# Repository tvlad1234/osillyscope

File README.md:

# osillyscope
CH32V003 OLED screen oscilloscope

 **Many thanks to [PCBway](https://www.pcbway.com/) for sponsoring this project with fast high-quality PCB prototyping.**

This is a small digital oscilloscope based around the CH32V003A4M6 RISC-V microcontroller. It uses an SSD1306 I2C OLED display and three pushbuttons for the user interface. Its purpose is to be an inexpensive, easy to build and pocket-sized tool for checking the presence, levels and waveform of an unknown signal. The hardware design focuses on simplicity and low-count bill of materials.

The maximum achievable sample rate is 1.6MSa/s (the time base goes as low as 5us/div). This project proposes a frontend design which allows for a signal input range between -3.3V and +3.3V. The input range can be extended using a standard 10x probe, as the instrument has 1MOhm of input impedance. The bandwidth of the frontend was measured to be around 2.5MHz. 

## Hardware
The schematics and board design files (KiCad 7) are provided in the [hw](hw) folder. Two PCB designs are included: [a 2-layer design, meant to be sent to a PCB fab](hw/osillyscope-2layer/) and [a single layer one, designed to be easily etchable](hw/osillyscope-etchable/).

### **PCBs**

Very shortly after I had published this project, PCBWay reached out to me, offering to try their PCB prototyping services. About a week after placing the order, the boards had arrived, and here are my thoughts on the service they provided:

I'm very pleased with them. They feel dense and solid, I had absolutely no trouble soldering them up. With such a relatively simple, untested board design, I chose to go with HASL finish. While assembling, I had to desolder and resolder the power pin header, and the pads didn't show any signs of possible failure or fatigue (I had that happen often with various circuit boards in the past, but I had no issues with these ones). Visually, I opted for black solder mask. It looks absolutely beautiful, glossy and uniformly coated, honestly the picture above doesn't show it in all of its beauty. The silkscreen is crisp, precise and nicely aligned.

Ordering from them was quite a breeze using their KiCad plugin, which automatically plots and uploads the Gerber files into their ordering platform with a single click. I find their service affordable, I ordered 10 boards (2 layers, 1.6mm with HASL finish) and the price for the boards came to be 5USD.

This was my first experience with PCBWay's prototyping service, and it's been a pleasant one. I will certainly consider them again for my next PCB prototyping needs, and I warmly encourage you too will give them a try.

### Circuitry  
The analog frontend consists of a 2x attenuator, opamp buffer stage and DC offset stage. An ICL7660 voltage converter IC provides the negative supply voltage for the TL082 dual opamp. The oscilloscope can be powered from a 5 or more volts supply, such as a 9V battery.

The schematics are also provided as PDF, in [doc/schematic.pdf](doc/schematic.pdf).

## Code
The firmware source code is provided in the [fw](fw) folder. It uses the [ch32fun](https://github.com/cnlohr/ch32fun/) framework.

The ADC operates in continuous conversion mode and samples are fetched into a circular buffer via DMA. Triggering is achieved using the analog watchdog feature of the ADC.

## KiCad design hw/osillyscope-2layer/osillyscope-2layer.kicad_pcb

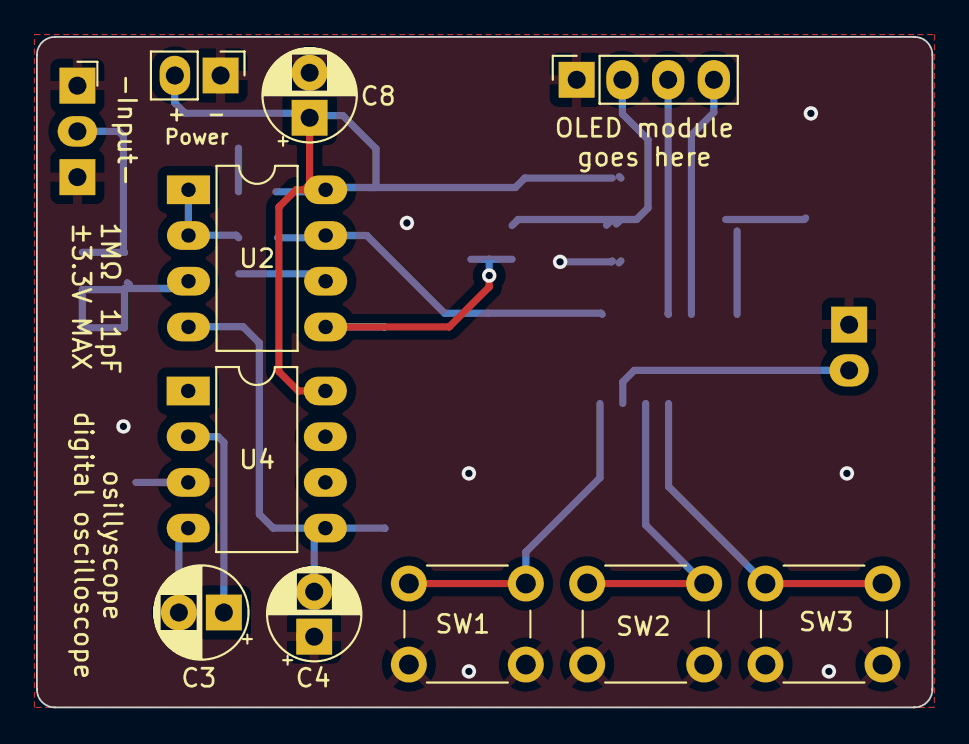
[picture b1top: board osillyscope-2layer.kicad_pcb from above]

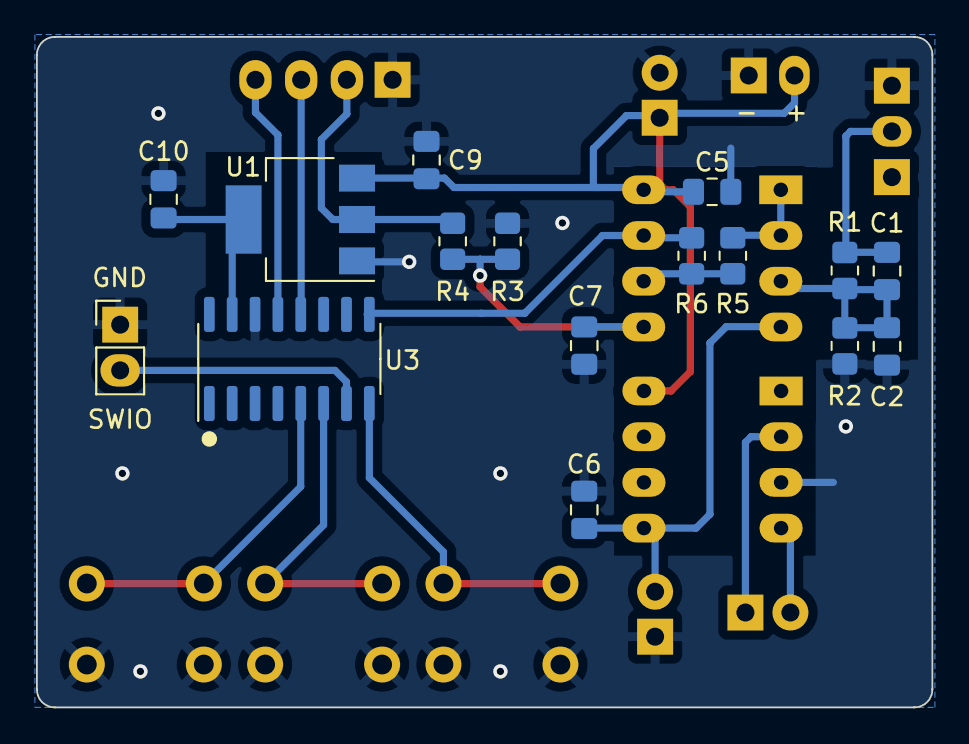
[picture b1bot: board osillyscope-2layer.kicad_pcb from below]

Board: 2 copper layers, 49.8 x 37.2 mm, 27 parts (16 on the bottom side), 18 nets.

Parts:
C1, C2: 22p; C_0805_2012Metric_Pad1.18x1.45mm_HandSolder
C3, C4: 10u; CP_Radial_D5.0mm_P2.50mm
C5, C6, C7, C9, C10: 100n; C_0805_2012Metric_Pad1.18x1.45mm_HandSolder
C8: 100u; CP_Radial_D5.0mm_P2.50mm
J1: IN; PinSocket_1x03_P2.54mm_Horizontal
J2: OLED; PinSocket_1x04_P2.54mm_Vertical
J3: Conn_01x02; PinHeader_1x02_P2.54mm_Vertical
J4: Debug/Prog; PinHeader_1x02_P2.54mm_Vertical
R1, R2: 500k; R_0805_2012Metric_Pad1.20x1.40mm_HandSolder
R3, R5, R6: 20k; R_0805_2012Metric_Pad1.20x1.40mm_HandSolder
R4: 60k; R_0805_2012Metric_Pad1.20x1.40mm_HandSolder
SW1: Decrement; SW_PUSH_6mm
SW2: Select; SW_PUSH_6mm
SW3: Increment; SW_PUSH_6mm
U1: AMS1117-3.3; SOT-223-3_TabPin2
U2: TL082; DIP-8_W7.62mm_LongPads
U3: CH32V003A4M6; SOIC-16_3.9x9.9mm_P1.27mm
U4: ICL7660; DIP-8_W7.62mm_LongPads

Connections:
+3.3V: C10.1, J2.2, R4.1, U1.2 (VO), U3.15 (VDD)
+5V: C5.1, C8.1, C9.2, J3.2, U1.3 (VI), U2.8 (V+), U4.8 (V+)
BTN_C: SW2.1, U3.6 (PC7)
BTN_L: SW1.1, U3.8 (PD4/A7)
BTN_R: SW3.1, U3.5 (PC6)
GND: C2.2, C4.1, C5.2, C6.1, C7.2, C8.2, C9.1, C10.2, J1.1, J1.3, J2.1, J3.1, J4.1, R2.2, R3.2, SW1.2, SW2.2, SW3.2, U1.1 (GND), U3.14 (VSS), U4.3 (GND)
IN+: C1.1, J1.2, R1.1
unnamed: C1.2, C2.1, R1.2, R2.1, U2.3 (+)
unnamed: R5.1, U2.1, U2.2 (-)
unnamed: R5.2, R6.2, U2.6 (-)
unnamed: C3.1, U4.2 (CAP+)
unnamed: C3.2, U4.4 (CAP-)
OUT_SIG: R6.1, U2.7, U3.9 (PD5/UTX/A5)
SCL: J2.3, U3.12 (PA1)
SDA: J2.4, U3.13 (PA2)
SWIO: J4.2, U3.7 (PD1/SWIO)
V_NEG: C4.2, C6.2, U2.4 (V-), U4.5 (VOUT)
V_OFFSET: C7.1, R3.1, R4.2, U2.5 (+)

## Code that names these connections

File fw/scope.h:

#ifndef _SCOPE_H
#define _SCOPE_H

#include <stdint.h>

#define DISP_BUF_LEN 64
#define CIRC_BUF_LEN (2 * DISP_BUF_LEN)

#define AN_IN_GPIO GPIOD
#define AN_IN_PIN 5
#define AN_IN_CH 5

#define BTN_R_GPIO GPIOC
#define BTN_R_PIN 6

#define BTN_C_GPIO GPIOC
#define BTN_C_PIN 7

#define BTN_L_GPIO GPIOD
#define BTN_L_PIN 4

#define volts_from_adc(s) ((frontend_offset - (3.3f * s / 1023.0f)) * 2.0f * atten)

enum
{
    TRIG_FALLING,
    TRIG_RISING
};

enum
{
    RUN_AUTO,
    RUN_NORM,
    RUN_END
};

enum
{
    NO_TRIGGER = 0,
    TRIG_FIRST,
    TRIG_SECOND,
    POST_TRIG,
    TRIG_DISABLED
};

extern float atten;
extern float frontend_offset;

struct Oscilloscope
{
    uint8_t runmode;

    uint16_t *wave_buf;
    uint16_t *adc_buf;

    volatile uint16_t trig_level;
    volatile uint8_t trig_slope;
    volatile uint8_t trig_state;
    volatile uint8_t awdg_trigged;

    volatile uint8_t dma_ready;
    volatile uint8_t dma_halves_filled;

    uint8_t tdiv_sel;
    uint8_t vdiv_sel;

    float samp_per;
    float atten;
    float frontend_offset;
};

typedef struct Oscilloscope oscilloscope_t;

void init_oscilloscope(oscilloscope_t *oscope);
void capture_waveform(oscilloscope_t *osc);

#endif

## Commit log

2024-11-03 refactor, change frontend voltage transf func, add sch and pcb
2024-11-03 Add image and pdf schematics, rephrase readme
2024-11-24 add 2layer board design, pcbway review
2025-12-17 add ch32fun as a submodule
2025-12-17 fix ADC interrupt flag and control bit clearing
2025-12-17 use circular buffer to capture pretrigger samples, not ready for production yet
2025-12-17 massive refactor to avoid using exported globals
2025-12-18 re-arm trigger on trigger point adjustment
2025-12-27 mention use of a circular buffer in readme
